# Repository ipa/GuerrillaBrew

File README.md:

GuerrillaBrew
=============

==Dependencies==
- boost 1.56 (http://www.boost.org/)

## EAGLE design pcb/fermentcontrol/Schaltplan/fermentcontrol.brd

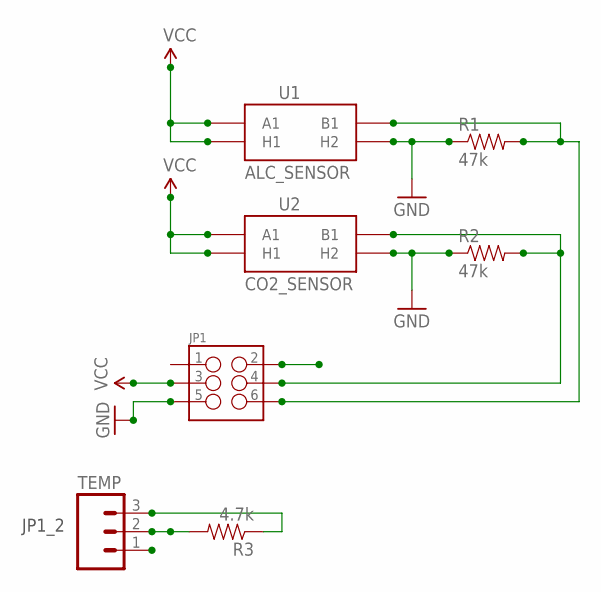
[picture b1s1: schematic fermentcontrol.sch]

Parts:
JP1: M03X2SHROUD; 2X3-SHROUDED
R1, R2: 47k; AXIAL-0.4
R3: 4.7k; AXIAL-0.4
TEMP: M03POLAR; MOLEX-1X3
U1: ALC_SENSOR; MQ-3
U2: CO2_SENSOR; MQ-3

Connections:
D01: JP1.2, R3.P$2 (2), TEMP.2
GND: JP1.5, R1.P$1 (1), R2.P$1 (1), TEMP.1, U1.HB (H2), U2.HB (H2)
unnamed: JP1.6, R1.P$2 (2), U1.B1
unnamed: JP1.4, R2.P$2 (2), U2.B1
VCC: JP1.3, R3.P$1 (1), TEMP.3, U1.A1, U1.HA (H1), U2.A1, U2.HA (H1)

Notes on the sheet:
JP1_2

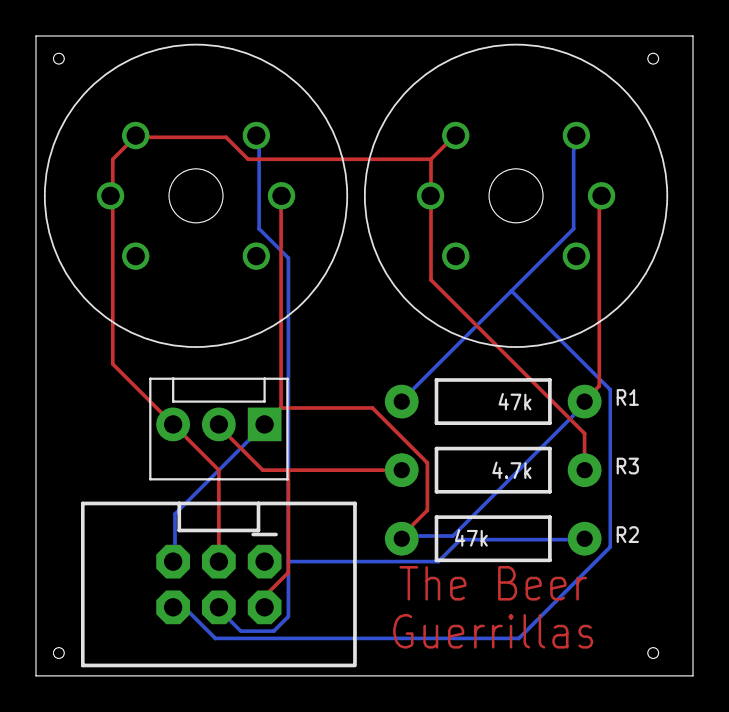
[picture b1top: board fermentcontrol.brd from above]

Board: 2 copper layers, 36.5 x 35.6 mm, 7 parts (0 on the bottom side), 5 nets.

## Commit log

2014-09-08 Qt project setup
2014-09-08 added some initial stuff to main window --> test on raspberry
2014-09-11 added fritzing schema for controller
2014-09-11 added dependency boost 1.56
2014-09-13 added example 2nd window
2014-09-13 start in fullscreen
2014-11-09 moved gui to subproject
2014-11-09 modified cmake
2014-11-09 make
2014-11-09 added bin to ignore
2014-11-12 added schematics and pcb of fermentcontroller
2014-11-12 modified pcb and routing to fit on smaller plate
2015-04-12 added fermentcontrol stuff
2016-04-09 fermentation control
2016-04-12 write to file
2016-04-12 fermentcontrol refactored
2016-04-13 added config, write to file, ds18b20 support
2016-04-13 workspace
2016-04-13 not working stuff
2016-04-13 added config
2016-04-13 added configurable interval
2016-04-13 added config for prod sensor
2016-04-13 added multiple sensors
2016-04-13 fixed temp sensor
2016-04-13 fixed config parser
2016-04-13 ignorefile and configuration
2016-04-14 fixed import configparser dependent on python version
2016-04-14 added toggle button to switch sensor
2016-04-14 add info on toggle button
2016-04-15 final version
2016-04-15 fixed gui
2016-04-22 moved pcb to hardware folder
2016-04-22 moved stuff to sandbox folder
2016-04-22 restructuring of the projects
2016-04-22 removed FermentationControl
2016-04-22 ignore .idea
2016-04-22 added flask app

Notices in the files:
parts and their libraries:
SparkFun-Resistors: Licensing: Creative Commons ShareAlike 4.0 International - https://creativecommons.org/licenses/by-sa/4.0
